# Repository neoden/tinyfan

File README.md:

# tinyfan

Temperature-controlled fan driver for a PC power supply. An ATtiny85 reads an
NTC thermistor and drives a standard 4-pin PWM fan from the PSU's own +5 V and
+12 V rails. Two-layer 26.55 × 18.05 mm board, all SMD parts on the top side,
designed in KiCad 10.

## How it works

| Block | Parts | Notes |
|---|---|---|
| MCU | U1 ATtiny85-20S (SOIC-8), C1 100 nF, R1 10 kΩ pull-up on RESET | Runs on +5 V |
| Temperature input | J3 (1×2), R2 10 kΩ, C2 100 nF | NTC between J3.1 and GND forms a divider with R2 to +5 V, filtered by C2, read on PB3/ADC3 |
| Fan PWM output | R3 1 kΩ, Q1 MMBT3904 | PB1 drives Q1 as an open-collector stage on the fan's PWM pin (J2.4) |
| Fan tach input | — | Fan tach (J2.3) goes to PB0 |
| Power | J1 (1×3) | +5 V, GND, +12 V from the PSU |

Connectors:

| Ref | Pins | Pinout |
|---|---|---|
| J1 | 1×3 | 1 = +5 V, 2 = GND, 3 = +12 V |
| J2 | 1×4 | 1 = GND, 2 = +12 V, 3 = TACH → PB0, 4 = PWM ← Q1 collector (standard 4-pin fan order) |
| J3 | 1×2 | 1 = NTC / ADC3, 2 = GND |

PB2 and PB4 are unused.

## Firmware

`firmware/tinyfan/tinyfan.ino` is an Arduino sketch for
[ATTinyCore](https://github.com/SpenceKonde/ATTinyCore), built with
`arduino-cli` (no IDE needed):

```sh
cd firmware
make deps                 # once: install the ATTinyCore board package
make                      # compile -> build/tinyfan.ino.hex
make fuses PROGRAMMER=usbasp   # once per chip: 8 MHz internal RC, BOD 4.3 V
make flash PROGRAMMER=usbasp   # upload over ISP
```

What it does, once a second:

1. Reads the NTC on ADC3 (16-sample average), converts with the Beta equation
   (10 kΩ @ 25 °C, B = 3435). Open or shorted sensor forces 100 %.
2. PI controller around a 55 °C setpoint: duty = 20 % + 3·err + 0.05·∫err,
   clamped to 20–100 %, integral clamped for anti-windup. Above 70 °C the fan
   goes to 100 % immediately.
3. Writes the duty to Timer1 PWM on PB1 at ~24 kHz. Q1 inverts it, so the
   register value is `TOP − duty`; at 100 % the output is detached and held
   low so Q1 is off and the fan's PWM line is released.

A 2 s watchdog restarts the chip if the loop stalls; the fan runs at 100 %
whenever PB1 is not actively driven (reset, boot, dead MCU).

The board has no ISP header. Program the ATtiny85 before soldering (SOIC-8
adapter) or with a SOIC-8 test clip. In-circuit, MISO (PB1) is loaded by
R3 and Q1's base, which may make clip programming unreliable.

## Layout

```
tinyfan.kicad_pro / .kicad_sch / .kicad_pcb   KiCad 10 project
gerbers/      Gerber X2 (Protel extensions) + Excellon drill, as sent to the fab
production/   bom.csv (JLCPCB columns), bom_pcbway.csv (hand-edited, with MPNs),
              tinyfan-all-pos.csv (JLCPCB CPL format, SMD parts only)
lib/          digispark_attiny85.kicad_sym — early Digispark symbol, not used by
              the current schematic (it uses the stock MCU_Microchip_ATtiny lib)
firmware/     ATtiny85 sketch + Makefile (arduino-cli, ATTinyCore)
Makefile      regenerates everything above with kicad-cli
```

## Regenerating outputs

Requires `kicad-cli` from KiCad 10 on `PATH` (override with `KICAD_CLI=...`).

```sh
make            # ERC + DRC, gerbers, drill, BOM, pos file
make zip        # build/tinyfan-gerbers.zip for the fab
make pdf        # build/tinyfan-schematic.pdf
```

ERC is clean. DRC reports 15 `silk_edge_clearance` warnings (J1 and J2
silkscreen outlines cross the board edge); `make drc` prints them but only
errors fail the build.

## BOM

| Ref | Value | Package | LCSC |
|---|---|---|---|
| C1, C2 | 100 nF | 0805 | C49678 |
| Q1 | MMBT3904 | SOT-23 | C20526 |
| R1, R2 | 10 kΩ | 0805 | C17414 |
| R3 | 1 kΩ | 0805 | C17513 |
| U1 | ATtiny85-20S | SOIC-8 | C89852 |
| J1–J3 | 2.54 mm right-angle pin headers | 1×3, 1×4, 1×2 | — |

## Working on it with Claude Code

The project is set up for the [`kicad` plugin](https://github.com/ProductOfAmerica/mcp-server-kicad)
(file-based KiCad MCP server, no running KiCad needed):

```sh
claude plugin marketplace add ProductOfAmerica/mcp-server-kicad
claude plugin install kicad
```

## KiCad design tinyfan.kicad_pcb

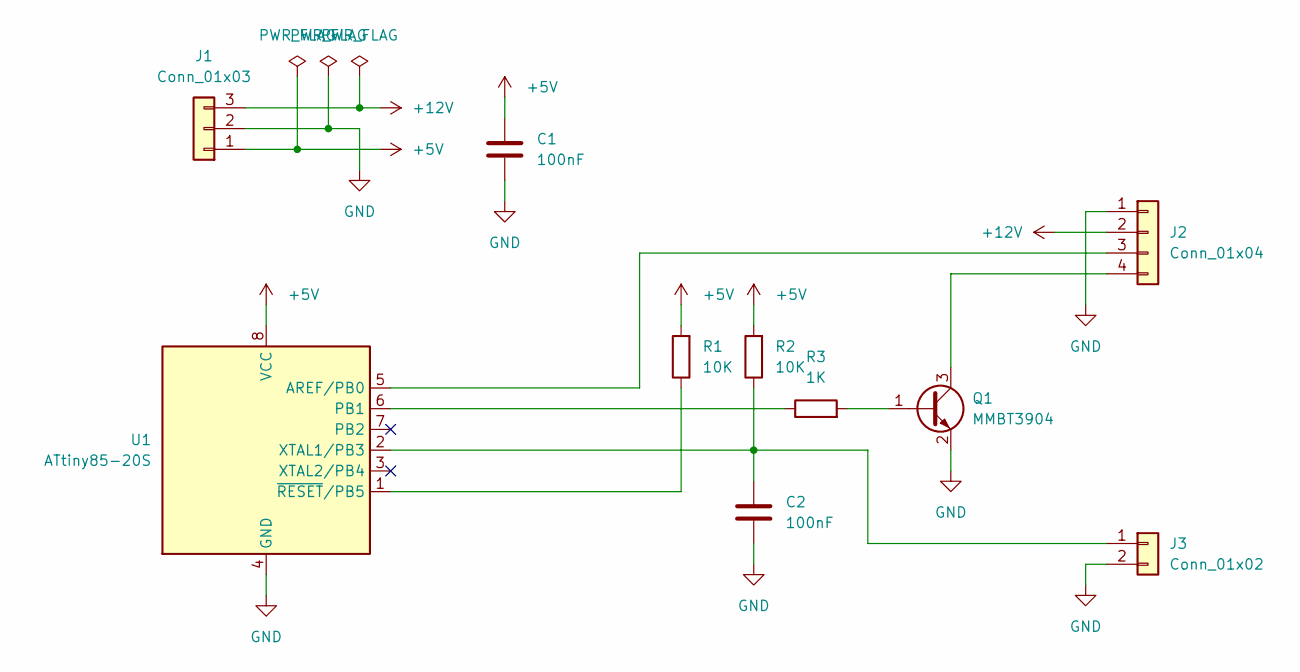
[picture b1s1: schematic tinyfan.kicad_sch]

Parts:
C1, C2: 100nF; C_0805_2012Metric; LCSC Part # C49678
J1: Conn_01x03; PinHeader_1x03_P2.54mm_Horizontal
J2: Conn_01x04; PinHeader_1x04_P2.54mm_Horizontal
J3: Conn_01x02; PinHeader_1x02_P2.54mm_Horizontal
Q1: MMBT3904; SOT-23; LCSC Part # C20526
R1, R2: 10K; R_0805_2012Metric; LCSC Part # C17414
R3: 1K; R_0805_2012Metric; LCSC Part # C17513
U1: ATtiny85-20S; SOIC-8_5.3x5.3mm_P1.27mm; LCSC Part # C89852

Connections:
+5V: C1.1, J1.1, R1.2, R2.2, U1.8 (VCC)
+12V: J1.3, J2.2
GND: C1.2, C2.2, J1.2, J2.1, J3.2, Q1.2 (E), U1.4 (GND)
unnamed: J2.3, U1.5 (AREF/PB0)
unnamed: J2.4, Q1.3 (C)
unnamed: C2.1, J3.1, R2.1, U1.2 (XTAL1/PB3)
unnamed: Q1.1 (B), R3.2
unnamed: R3.1, U1.6 (PB1)
unnamed: R1.1, U1.1 (~RESET/PB5)

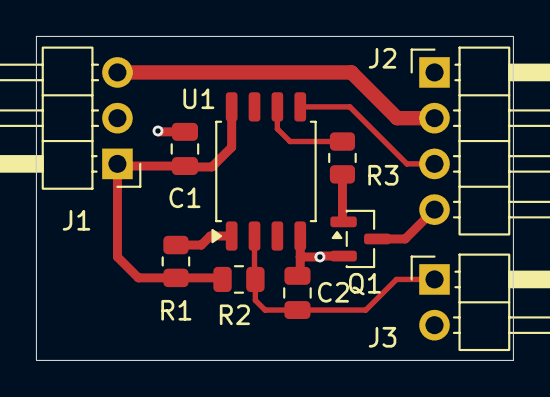
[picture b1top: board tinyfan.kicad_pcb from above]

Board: 2 copper layers, 26.5 x 18.0 mm, 10 parts (0 on the bottom side), 9 nets.

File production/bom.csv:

"Designator","Comment","Footprint","LCSC Part #"
"C1,C2","100nF","Capacitor_SMD:C_0805_2012Metric","C49678"
"Q1","MMBT3904","Package_TO_SOT_SMD:SOT-23","C20526"
"R1,R2","10K","Resistor_SMD:R_0805_2012Metric","C17414"
"R3","1K","Resistor_SMD:R_0805_2012Metric","C17513"
"U1","ATtiny85-20S","Package_SO:SOIC-8_5.3x5.3mm_P1.27mm","C89852"
